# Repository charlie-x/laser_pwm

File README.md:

# laser_pwm

3v to 5v with LC filter

Eagle 7, with gerbers for CNC board, single sided. tested on 40W laser and Analog/PWM IN power supply.

I had better results with this, than with the transistor methods, or bi directional shifters, this level shifter can run faster too.

used the 5v vreg added to the smooothieboard as the 5v source

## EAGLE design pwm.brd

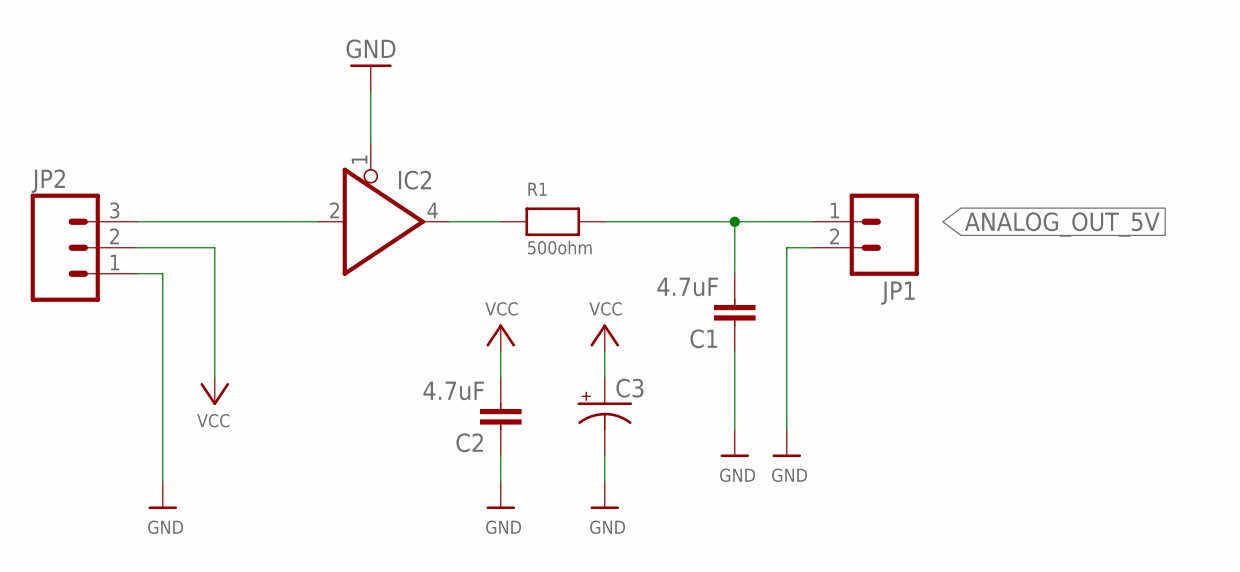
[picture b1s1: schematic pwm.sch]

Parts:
C1, C2: 4.7uF; 1206
C3: CPOL-USE; PANASONIC_E
IC2: 74AHCT1G125DBV; SOT23-5; PARTNO M74VHC1GT125DF2G; DIGIKEY-ND M74VHC1GT125DF1GOSCT-ND
JP1: M02LOCK_LONGPADS; 1X02_LOCK_LONGPADS
JP2: M03LONGPADS; 1X03_LONGPADS
R1: 500ohm; 1206

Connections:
ANALOG_OUT_5V: C1.2, JP1.1, R1.2
GND: C1.1, C2.1, C3.-, IC2.1 (OE), IC2.3 (GND), JP1.2, JP2.1
unnamed: IC2.4 (O), R1.1
PWM_IN_3V: IC2.2 (I), JP2.3
VCC: C2.2, C3.+, IC2.5 (VCC), JP2.2

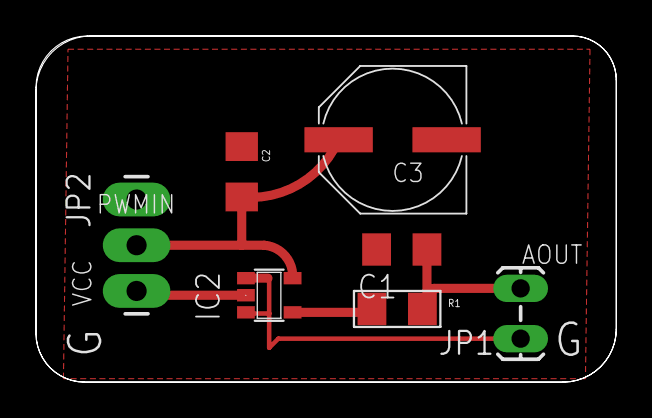
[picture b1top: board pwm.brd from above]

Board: 2 copper layers, 32.2 x 19.2 mm, 7 parts (0 on the bottom side), 5 nets.

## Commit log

2016-07-11 added files
    tested.
2016-07-11 notes

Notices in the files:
parts and their libraries:
SparkFun-Capacitors: Licensing: CC v3.0 Share-Alike You are welcome to use this library for commercial purposes.
microbuilder: This work is placed in the public domain, and may be freely used for commercial and non-commercial work with the following conditions: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
